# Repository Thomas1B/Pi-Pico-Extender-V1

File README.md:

# Raspberry Pi Pico Extender V1

This is a custom extender board for the Raspberry Pi Pico (https://www.raspberrypi.com/products/raspberry-pi-pico/).

It allows full use of the breadboard when prototyping and the pins labels on top for easier reference. The board also contains a USB-C connection for aux power (3V3 and 5V) if needed for high power components.

The board is designed with the same dimensions as a Pi Hat for easy mounting.

<hr>

 (coming soon!)

<hr>

See `Pi Pico Extender V1 DigiKey BOM.csv` for components list.<br>
See `Pi Pico Extender KiCad BOM.csv` for parts reference.

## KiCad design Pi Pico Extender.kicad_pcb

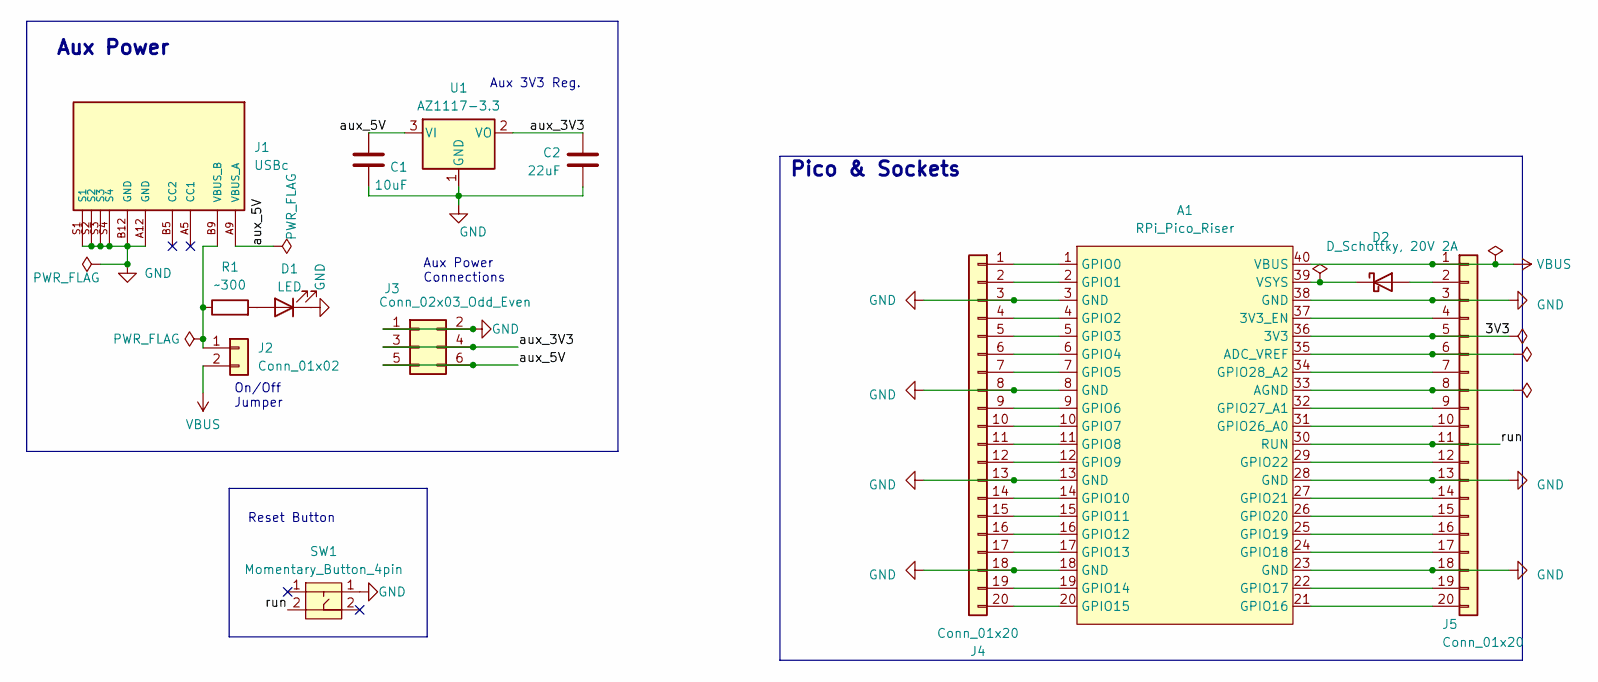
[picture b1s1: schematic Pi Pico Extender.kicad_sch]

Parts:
A1: RPi_Pico_Riser; RPi_Pico Riser
C1: 10uF; C_0805_2012Metric_Pad1.18x1.45mm_HandSolder
C2: 22uF; C_0805_2012Metric_Pad1.18x1.45mm_HandSolder
D1: LED; LED_0805_2012Metric_Pad1.15x1.40mm_HandSolder
D2: D_Schottky, 20V 2A; D_SOD-123F
J1: USBc; GCT_USB4125-GF-A_REVA2
J2: Conn_01x02; PinHeader_1x02_P2.54mm_Vertical
J3: Conn_02x03_Odd_Even; PinSocket_2x03_P2.54mm_Vertical
J4, J5: Conn_01x20; PinSocket_1x20_P2.54mm_Vertical
R1: ~300; R_0805_2012Metric_Pad1.20x1.40mm_HandSolder
SW1: Momentary_Button_4pin; SW_PUSH_6mm
U1: AZ1117-3.3; SOT-223-3_TabPin2

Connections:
/3V3: A1.36 (3V3), J5.5
/aux_3V3: C2.2, J3.3, J3.4, U1.2 (VO)
/aux_5V: C1.2, J1.A9 (VBUS_A), J3.5, J3.6, U1.3 (VI)
/run: A1.30 (RUN), J5.11, SW1.2
GND: A1.3 (GND), A1.8 (GND), A1.13 (GND), A1.18 (GND), A1.23 (GND), A1.28 (GND), A1.38 (GND), C1.1, C2.1, D1.1 (K), J1.A12 (GND), J1.B12 (GND), J1.S1, J1.S2, J1.S3, J1.S4, J3.1, J3.2, J4.3, J4.8, J4.13, J4.18, J5.3, J5.13, J5.18, SW1.1, U1.1 (GND)
unnamed: A1.37 (3V3_EN), J5.4
unnamed: A1.35 (ADC_VREF), J5.6
unnamed: A1.33 (AGND), J5.8
unnamed: A1.1 (GPIO0), J4.1
unnamed: A1.2 (GPIO1), J4.2
unnamed: A1.4 (GPIO2), J4.4
unnamed: A1.5 (GPIO3), J4.5
unnamed: A1.6 (GPIO4), J4.6
unnamed: A1.7 (GPIO5), J4.7
unnamed: A1.9 (GPIO6), J4.9
unnamed: A1.10 (GPIO7), J4.10
unnamed: A1.11 (GPIO8), J4.11
unnamed: A1.12 (GPIO9), J4.12
unnamed: A1.14 (GPIO10), J4.14
unnamed: A1.15 (GPIO11), J4.15
unnamed: A1.16 (GPIO12), J4.16
unnamed: A1.17 (GPIO13), J4.17
unnamed: A1.19 (GPIO14), J4.19
unnamed: A1.20 (GPIO15), J4.20
unnamed: A1.21 (GPIO16), J5.20
unnamed: A1.22 (GPIO17), J5.19
unnamed: A1.24 (GPIO18), J5.17
unnamed: A1.25 (GPIO19), J5.16
unnamed: A1.26 (GPIO20), J5.15
unnamed: A1.27 (GPIO21), J5.14
unnamed: A1.29 (GPIO22), J5.12
unnamed: A1.31 (GPIO26_A0), J5.10
unnamed: A1.32 (GPIO27_A1), J5.9
unnamed: A1.34 (GPIO28_A2), J5.7
unnamed: A1.39 (VSYS), D2.1 (K)
unnamed: D1.2 (A), R1.2
unnamed: D2.2 (A), J5.2
unnamed: J1.B9 (VBUS_B), J2.1, R1.1
VBUS: A1.40 (VBUS), J2.2, J5.1

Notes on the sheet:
Pico & Sockets
Aux Power
On/Off Jumper
Aux 3V3 Reg.
Reset Button
Aux Power Connections

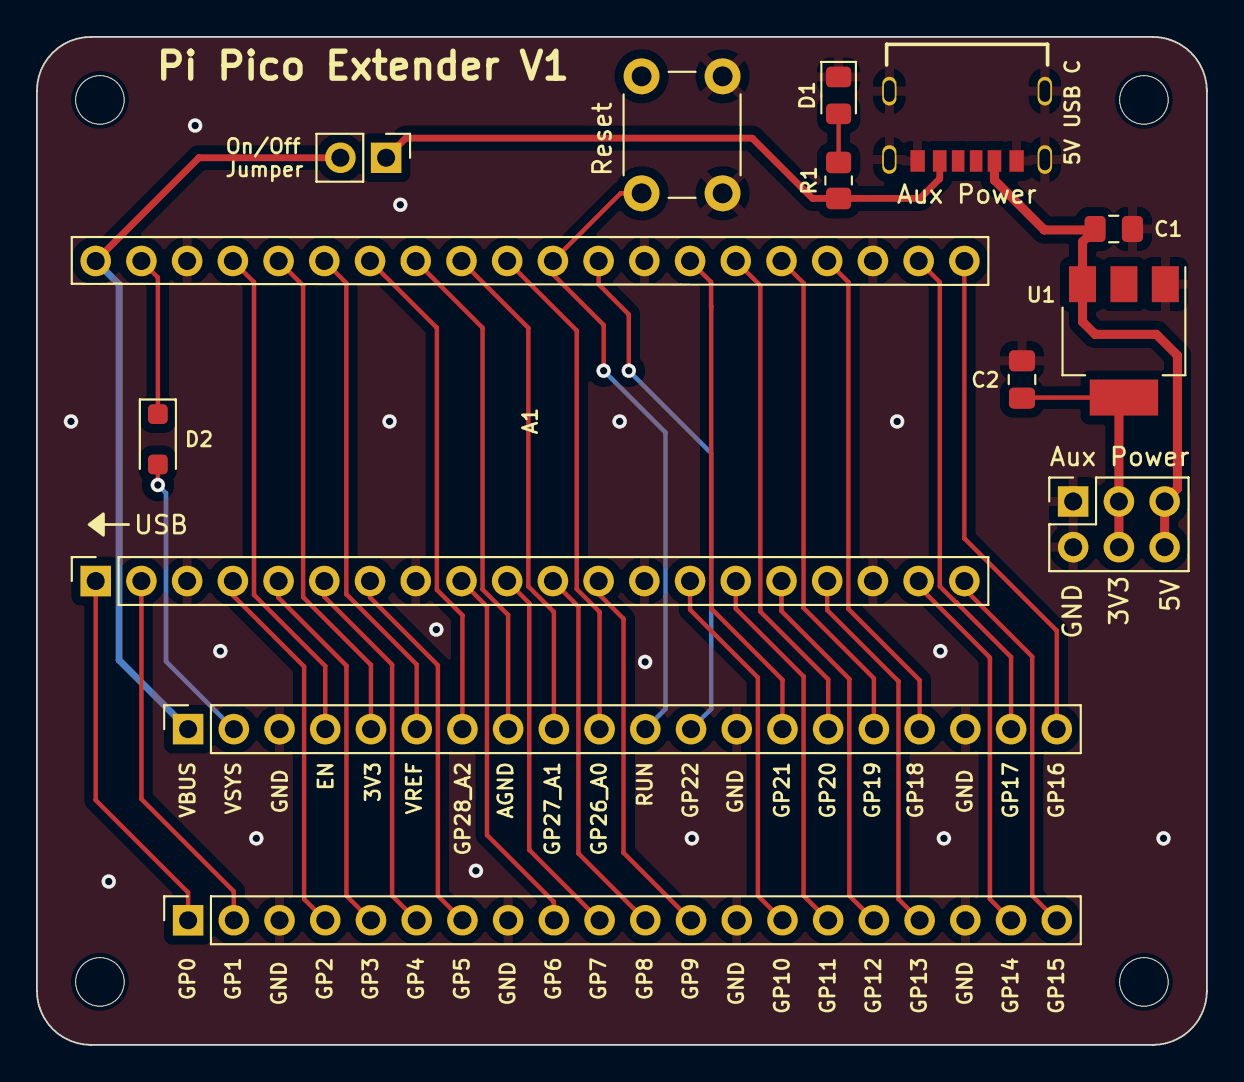
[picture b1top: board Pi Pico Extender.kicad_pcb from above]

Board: 2 copper layers, 65.0 x 56.0 mm, 17 parts (0 on the bottom side), 39 nets.

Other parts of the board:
MH1, MH2, MH3, MH4: MountingHole_2.7mm_M2.5

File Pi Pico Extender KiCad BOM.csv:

"Project:","Pi Pico Extender\Pi Pico Extender.kicad_sch"
"Date:","10/5/2023"
"Tool:","Eeschema 7.0.6"
"BOM Generator:","myScripts\myKiCad_BOM_Maker.py"

"Total Component Count:","13"
"Component Type Count:","12"
"Ref","Qnty","Value","Description","Cmp name","Footprint"

"Component: 1/12:"
"A1","1","RPi_Pico_Riser","RPi Pico Riser, 2 01x20 p2.54mm pinSockets","RPi_Pico_Riser","0_Thomas_Footprints:RPi_Pico Riser"

"Component: 2/12:"
"C1","1","10uF","Unpolarized capacitor","C","Capacitor_SMD:C_0805_2012Metric_Pad1.18x1.45mm_HandSolder"

"Component: 3/12:"
"C2","1","22uF","Unpolarized capacitor","C","Capacitor_SMD:C_0805_2012Metric_Pad1.18x1.45mm_HandSolder"

"Component: 4/12:"
"D1","1","LED","Light emitting diode","LED","LED_SMD:LED_0805_2012Metric_Pad1.15x1.40mm_HandSolder"

"Component: 5/12:"
"D2","1","D_Schottky, 20V 2A","Schottky diode","D_Schottky","Diode_SMD:D_SOD-123F"

"Component: 6/12:"
"J1","1","USBc","USB C Socket- 6 pin","USB C Socket- 6 pin","0_Thomas_Footprints:GCT_USB4125-GF-A_REVA2"

"Component: 7/12:"
"J2","1","Conn_01x02","Generic connector, single row, 01x02","Conn_01x02","Connector_PinHeader_2.54mm:PinHeader_1x02_P2.54mm_Vertical"

"Component: 8/12:"
"J3","1","Conn_02x03_Odd_Even","Generic connector, double row, 02x03, odd/even pin numbering scheme (row 1 odd numbers, row 2 even numbers)","Conn_02x03_Odd_Even","Connector_PinSocket_2.54mm:PinSocket_2x03_P2.54mm_Vertical"

"Component: 9/12:"
"J4, J5","2","Conn_01x20","Generic connector, single row, 01x20","Conn_01x20","Connector_PinSocket_2.54mm:PinSocket_1x20_P2.54mm_Vertical"

"Component: 10/12:"
"R1","1","~300","Resistor","R","Resistor_SMD:R_0805_2012Metric_Pad1.20x1.40mm_HandSolder"

"Component: 11/12:"
"SW1","1","Momentary_Button_4pin","4 pin pushbutton","Momentary_Button_4pin","Button_Switch_THT:SW_PUSH_6mm"

"Component: 12/12:"
"U1","1","AZ1117-3.3","1A 20V Fixed LDO Linear Regulator, 3.3V, SOT-89/SOT-223/TO-220/TO-252/TO-263","AZ1117-3.3","Package_TO_SOT_SMD:SOT-223-3_TabPin2"

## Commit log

2023-10-09 syncing files
2023-10-09 Create LICENSE
2023-10-10 syncing
